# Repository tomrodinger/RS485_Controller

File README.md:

# Gearotons RS485 Controller

A programmable ESP32-S3 board with a half-duplex RS485 interface for Gearotons servomotors and other RS485 devices. The product includes an external antenna. One unit weighs **11.7 g including the antenna**.

## Documentation

[RS485 Controller hardware 0.5 documentation](https://9o.at/products/rs2/0.5) includes the datasheet, schematic and product photographs. The QR code printed on the PCB resolves to this page. Its content is generated from [`PRODUCT_DATA.yaml`](PRODUCT_DATA.yaml), using the same system as the RS485 Adapter and M17 Servomotor.

## Datasheet

[Download the RS485 Controller datasheet v1.0 (PDF)](datasheet/rs485_controller_datasheet_v1.0.pdf). Covers PCB revision 0.5, connector pinouts, two-motor wiring, mechanical dimensions, breakout headers, Arduino setup and the controller schematic.

## Hardware

The latest numbered PCB revision is **0.5**, in [`PCB/0.5`](PCB/0.5). Open `0.5.kicad_pro` in KiCad; the design was last saved with KiCad 9. The board outline is 48.89 × 36.88 mm, with a nominal PCB thickness of 1.6 mm. These dimensions exclude connector and antenna protrusions.

- ESP32-S3-MINI-1U module with external antenna connector.
- SP3485EN RS485 transceiver; automatic transmit direction circuitry.
- RS485 UART: GPIO4 TX and GPIO5 RX. The supplied demos use 230400 baud, 8N1.
- J5, marked **USB-C PROG**, connects to the ESP32-S3 native USB interface and the 5 V input rail.
- J3, marked **USB-C PD POWER IN**, uses a CH221K to request 20 V with R27 = 200 kΩ. R31 is an optional, unpopulated resistor in the standard design.
- J1, marked **POWER OUT**, exposes the J3 power rail directly: pin 1 positive, pin 2 GND. Actual output voltage depends on the connected supply and PD negotiation. Check the voltage before connecting motors.
- J2 pins 1–8: **GND, A, B, GND, A, B, 3.3 V, 5 V**. The two A/B/GND groups share one bus. Use the PCB labels to identify orientation.

Connect A to A, B to B, and controller GND to the motors' common ground. Motor power must use the appropriate motor supply, never J2's 3.3 V or 5 V pins. The board is not galvanically isolated. A board-level motor-current rating has not been established.

## Programming

Program the ESP32-S3 through J5 using a suitable ESP32-S3 toolchain, such as the Arduino ESP32 core with the Gearotons Servomotor library. Configure RS485 UART RX on GPIO5 and TX on GPIO4. The controller's USB-to-RS485 bridging and wireless application behavior depend on the firmware you install.

## Product images

[`images/rs485-controller`](images/rs485-controller) contains real product photographs, metadata-free JPEGs, full-resolution WebP images and 800-pixel WebP variants. [`manifest.json`](images/rs485-controller/manifest.json) supplies filenames, dimensions, alt text and original source hashes. These paths can be served directly from the public repository; use a pinned commit URL for immutable ecommerce assets.

## Validation of the 0.5 upload

On 2026-10-26, KiCad 9.0.7 error-level DRC with schematic parity reported zero violations, zero unconnected items and zero schematic parity issues. This is a design-file check, not an electrical or thermal qualification of manufactured hardware.

## Maintaining the documentation

The [maintainer handoff](datasheet/README.md#maintainer-handoff--4-november-2026), including its **5 November 2026 context-reset checkpoint**, records the accepted datasheet and diagram decisions, current 14-page PDF checksum, photo-edit sources, corrected pin/power guidance, build/verification commands, publication evidence and remaining limitations. Read it before continuing work after a context reset.

[`diagram-review/README.md`](diagram-review/README.md) preserves the artwork iterations and electrical-review history. [`motor_control_demo/README.md`](motor_control_demo/README.md) explains the separate Arduino examples. The unfinished archive in `PCB/V1_not_completed` is separate from the released PCB 0.5 design.

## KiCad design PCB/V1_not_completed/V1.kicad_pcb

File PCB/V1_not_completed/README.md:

# Unfinished design archive

This directory contains hardware work that predates the datasheet task and is retained as an unfinished development archive. Its library files and manufacturing exports are not the released RS485 Controller design.

The released product remains **RS2 / PCB revision 0.5** in [`../0.5`](../0.5), covered by datasheet document revision 1.0. Do not interpret this directory name as a released hardware version or use these fabrication exports as the production package for PCB 0.5.

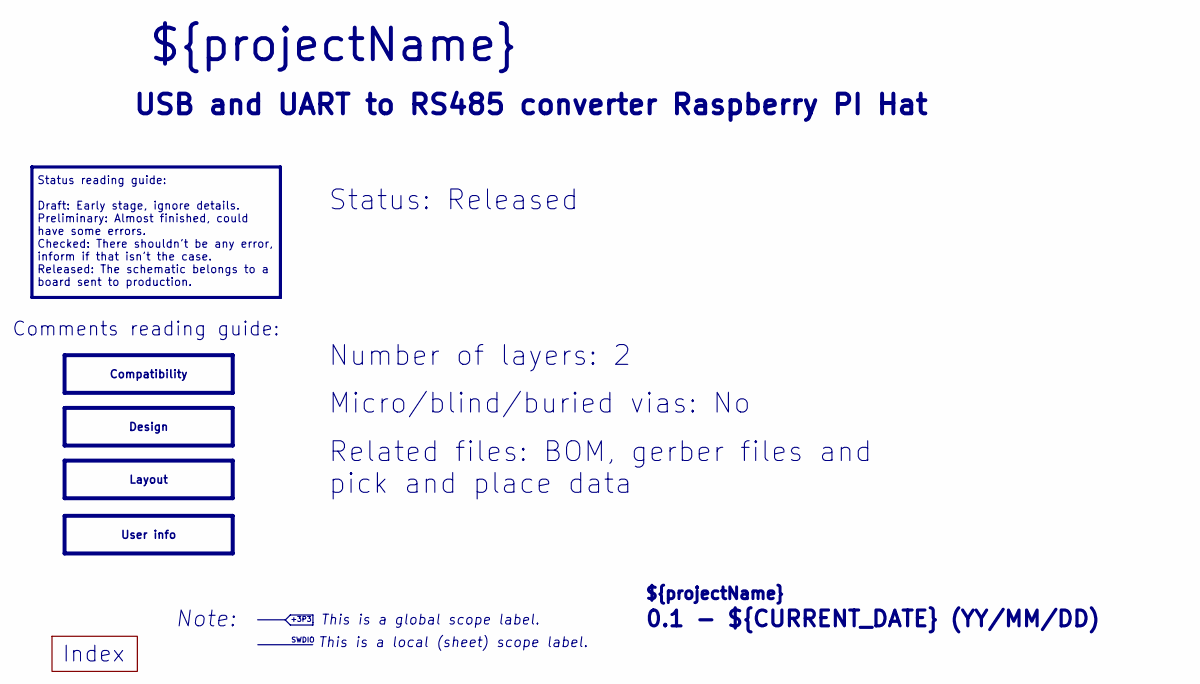
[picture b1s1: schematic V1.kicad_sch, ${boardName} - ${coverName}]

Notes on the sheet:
${REVISION} - ${CURRENT_DATE} (YY/MM/DD)
Status reading guide: Draft: Early stage, ignore details. Preliminary: Almost finished, could have some errors. Checked: There shouldn't be any error, inform if that isn't the case. Released: The schematic belongs to a board sent to production.
${projectName}
This is a global scope label.
Micro/blind/buried vias: No
Status: Released
Comments reading guide:
Note:
USB and UART to RS485 converter Raspberry PI Hat
Related files: BOM, gerber files and pick and place data
This is a local (sheet) scope label.
SWDIO
Index
+3P3
Number of layers: 2
Design
Compatibility
User info
Layout

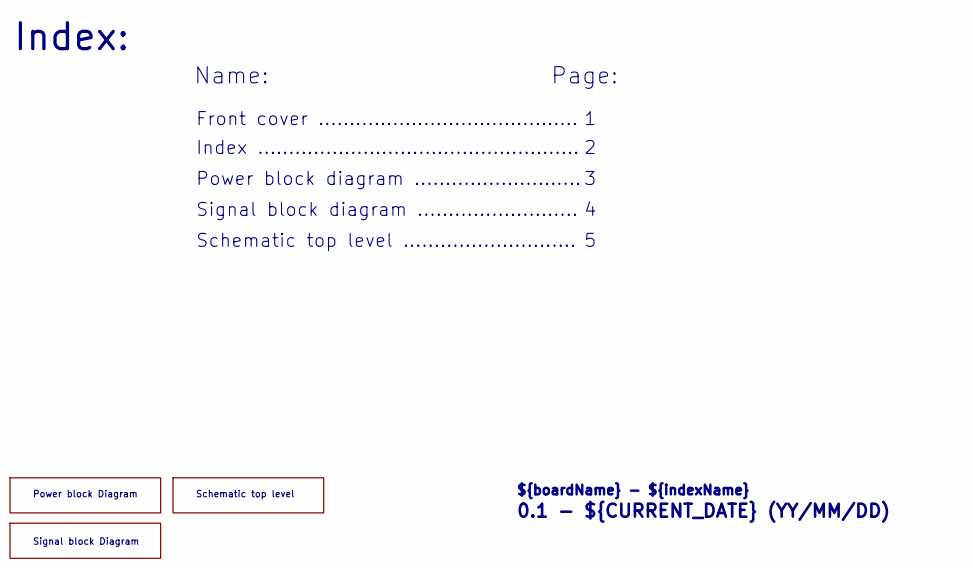
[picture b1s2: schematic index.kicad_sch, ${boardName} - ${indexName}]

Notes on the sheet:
Power block Diagram
Front cover ..........................................
Schematic top level
${boardName} - ${indexName}
Schematic top level ............................
Index ....................................................
${REVISION} - ${CURRENT_DATE} (YY/MM/DD)
Signal block diagram ..........................
Signal block Diagram
Name:
Page:
Power block diagram ...........................
Index:

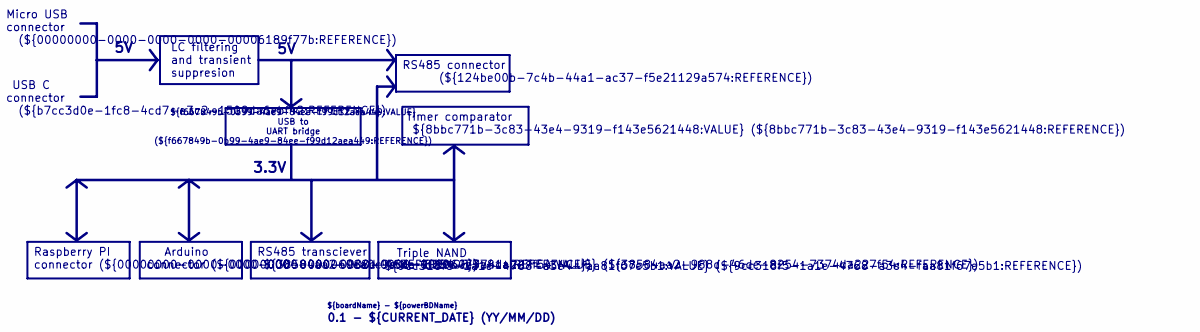
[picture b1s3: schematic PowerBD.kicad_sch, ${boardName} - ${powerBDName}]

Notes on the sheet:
Arduino connector (${00000000-0000-0000-0000-000060e9a81a:REFERENCE})
RS485 connector (${124be00b-7c4b-44a1-ac37-f5e21129a574:REFERENCE})
Triple NAND ${9cc318f5-1a1e-4768-a3e4-faa81f67e5b1:VALUE} (${9cc318f5-1a1e-4768-a3e4-faa81f67e5b1:REFERENCE})
Raspberry PI connector (${00000000-0000-0000-0000-000060ea0c9e:REFERENCE})
RS485 transciever ${38584aa2-988d-46de-8254-7374da227f54:VALUE} (${38584aa2-988d-46de-8254-7374da227f54:REFERENCE})
LC filtering and transient suppresion
${REVISION} - ${CURRENT_DATE} (YY/MM/DD)
USB C connector (${b7cc3d0e-1fc8-4cd7-a3c2-1509da6ebf42:REFERENCE})
Timer comparator ${8bbc771b-3c83-43e4-9319-f143e5621448:VALUE} (${8bbc771b-3c83-43e4-9319-f143e5621448:REFERENCE})
${boardName} - ${powerBDName}
Micro USB connector (${00000000-0000-0000-0000-00006189f77b:REFERENCE})
3.3V
${f667849b-0b99-4ae9-84ee-f99d12aea449:VALUE} USB to UART bridge (${f667849b-0b99-4ae9-84ee-f99d12aea449:REFERENCE})

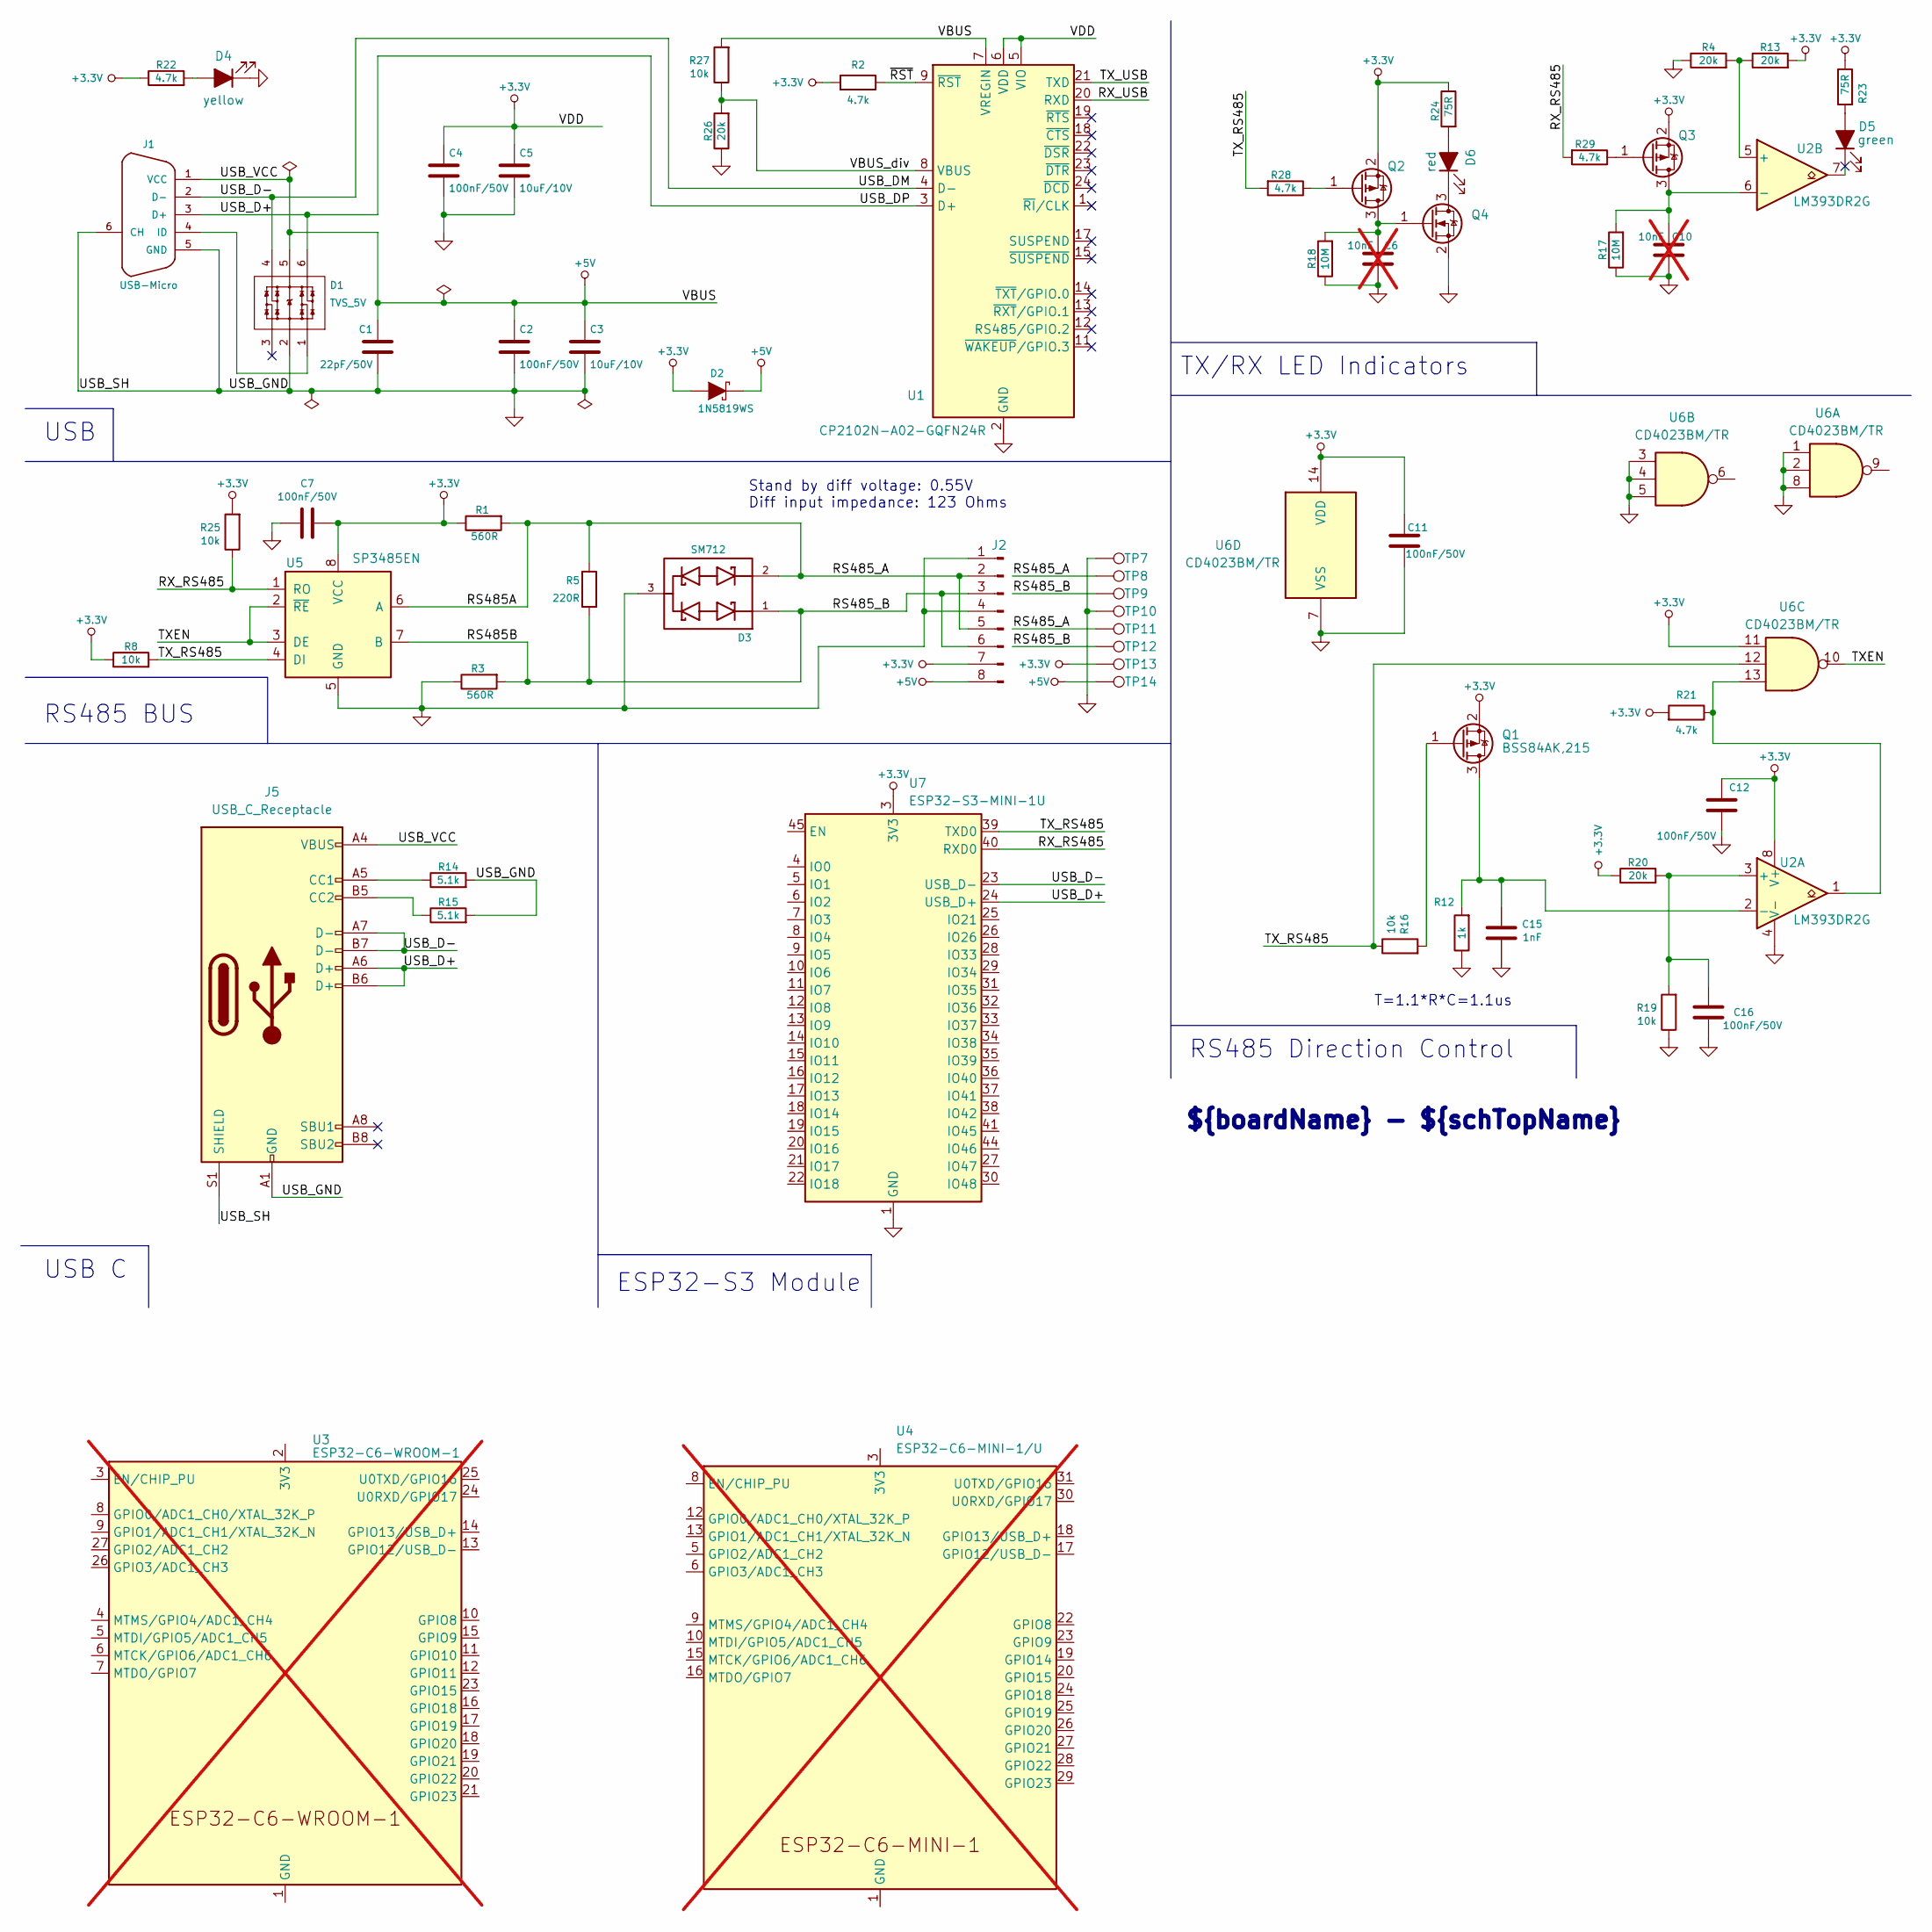
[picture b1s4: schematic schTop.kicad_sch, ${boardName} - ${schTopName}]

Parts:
C1: 22pF/50V; C_0603_1608Metric; Tolerance 5%; PartNumber CL10C220JB8NNNC; Digikey 1276-1023-1-ND
C2, C4, C7, C11, C12, C16: 100nF/50V; C_0603_1608Metric; Tolerance 10%; PartNumber CC0603KRX7R9BB104; Digikey 1276-6854-1-ND
C3, C5: 10uF/10V; C_0603_1608Metric; Tolerance 10%; PartNumber CL10A106KP8NNNC; LCSC C19702
C6: 10nF; C_0603_1608Metric; Tolerance 10%; PartNumber 0603B103K500NT; LCSC C57112; not fitted
C10: 10nF; C_0603_1608Metric; Tolerance 10%; PartNumber 0603B103K500NT; Digikey ---; not fitted
C15: 1nF; C_0603_1608Metric; Tolerance 10%; PartNumber CL10B102KB8NNNC; LCSC C1588
D1: TVS_5V; SOT23-6L; Tolerance _; PartNumber TPIP4220CZ6; Digikey !1727-2751-1-ND
D2: 1N5819WS; SOD323; LCSC C191023
D3: SM712; SOT23-3; Tolerance _; PartNumber SM712; Digikey !F6450CT-ND
D4: yellow; LED_0805_2012Metric; PartNumber KT-0805Y; LCSC C2296
D5: green; LED_0805_2012Metric; PartNumber KT-0805G; LCSC C2297
D6: red; LED_0805_2012Metric; PartNumber NCD0805R1; LCSC C84256
J1: USB-Micro; usb-MicroXNJ; Tolerance _; PartNumber MicroXNJ; Digikey !732-5961-1-ND
J2: TSM-108-01-T-SH-A-P-TR; SAMTEC_TSM-108-01-T-SH-A-P-TR_hole1.5mm
J5: USB_C_Receptacle; USB_C_Receptacle_Palconn_UTC16-G; LCSC C2765186
Q1, Q2, Q3: BSS84AK,215; SOT-23; Tolerance _; PartNumber BSS84AK,215; Digikey ---
Q4: Q_NMOS_GSD; SOT-23; Part Number 2N7002; LCSC C8545
R1, R3: 560R; R_0603_1608Metric; Tolerance 1%; PartNumber 0603WAF5600T5E; LCSC C23204
R2, R21, R22, R28, R29: 4.7k; R_0603_1608Metric; Tolerance 1%; PartNumber 0603WAF4701T5E; LCSC C23162
R4, R13, R20, R26: 20k; R_0603_1608Metric; Tolerance 1%; PartNumber 0603WAF2002T5E; LCSC C4184
R5: 220R; R_0603_1608Metric; Tolerance 5%; PartNumber 0603WAF2200T5E; LCSC C22962
R8, R16, R19, R25, R27: 10k; R_0603_1608Metric; Tolerance 1%; PartNumber 0603WAF1002T5E; LCSC C25804
R12: 1k; R_0603_1608Metric; Tolerance 1%; PartNumber 0603WAF1001T5E; Digikey 311-1.00KHRCT-ND
R14, R15: 5.1k; R_0402_1005Metric; Tolerance 1%; LCSC C25905
R17, R18: 10M; R_0603_1608Metric; PartNumber 0603WAF1005T5E; LCSC C7250
R23, R24: 75R; R_0603_1608Metric; Tolerance 1%; PartNumber 0603WAF750JT5E; LCSC C4275
TP7, TP8, TP9, TP10, TP11, TP12, TP13, TP14: TestPoint; testpoint_no_border
U1: CP2102N-A02-GQFN24R; QFN-24-1EP_4x4mm_P0.5mm_EP2.6x2.6mm; Tolerance _; PartNumber CP2102N-A02-GQFN24R; Digikey _
U2: LM393DR2G; SOIC-8_3.9x4.9mm_P1.27mm; Tolerance _; PartNumber LM393DR2G; Digikey _
U3: ESP32-C6-WROOM-1; not fitted
U4: ESP32-C6-MINI-1/U; ESP32-C6-MINI-1; not fitted
U5: SP3485EN; SOIC-8_3.9x4.9mm_P1.27mm; Tolerance _; PartNumber SP3485EN-L/TR; LCSC C8963
U6: CD4023BM/TR; SOIC-14_3.9x8.7mm_P1.27mm; Tolerance _; PartNumber CD4023BM/TR; Digikey _
U7: ESP32-S3-MINI-1U; ESP32-S2-MINI-1U

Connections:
+3.3V: C4.1, C5.1, C7.2, C11.2, C12.2, D2.1 (A), J2.7, Q1.2 (S), Q2.2 (S), Q3.2 (S), R1.1, R2.2, R8.1, R13.2, R20.1, R21.2, R22.1, R23.1, R24.1, R25.2, TP13.1, U1.5 (VIO), U1.6 (VDD), U2.8 (V+), U5.8 (VCC), U6.11, U6.14 (VDD), U7.3 (3V3); also elsewhere on the board
+5V: C1.1, C2.1, C3.1, D1.5 (VDD), D2.2 (K), J1.1 (VCC), J2.8, J5.A4 (VBUS), J5.A9 (VBUS), J5.B4 (VBUS), J5.B9 (VBUS), R27.2, TP14.1, U1.7 (VREGIN)
/index/schTop/RS485A: D3.2 (cathode), J2.2, J2.5, R1.2, R5.1, TP8.1, TP11.1, U5.6 (A)
/index/schTop/RS485B: D3.1 (Anode), J2.3, J2.6, R3.2, R5.2, TP9.1, TP12.1, U5.7 (B)
/index/schTop/RX_RS485: R25.1, R29.2, U5.1 (RO), U7.40 (RXD0)
/index/schTop/RX_USB: U1.20 (RXD)
/index/schTop/TXEN: U5.2 (~RE), U5.3 (DE), U6.10
/index/schTop/TX_RS485: R8.2, R16.1, R28.2, U5.4 (DI), U6.12, U7.39 (TXD0)
/index/schTop/TX_USB: U1.21 (TXD)
/index/schTop/USB_D+: D1.6 (IO4), J1.3 (D+), J5.A6 (D+), J5.B6 (D+), U1.3 (D+), U7.24 (USB_D+)
/index/schTop/USB_D-: D1.4 (IO3), J1.2 (D-), J5.A7 (D-), J5.B7 (D-), U1.4 (D-), U7.23 (USB_D-)
/index/schTop/VBUS_div: R26.2, R27.1, U1.8 (VBUS)
/index/schTop/~RST: R2.1, U1.9 (~RST)
GND: C1.2, C2.2, C3.2, C4.2, C5.2, C6.1, C7.1, C10.1, C11.1, C12.1, C15.1, C16.1, D1.2 (GND), D3.3 (AK), D4.1 (K), J1.5 (GND), J1.6 (CH), J2.1, J2.4, J5.A1 (GND), J5.A12 (GND), J5.B1 (GND), J5.B12 (GND), J5.S1 (SHIELD), Q4.2 (S), R3.1, R4.1, R12.1, R14.2, R15.2, R17.1, R18.1, R19.1, R26.1, TP7.1, TP10.1, U1.2 (GND), U1.25 (GND), U2.4 (V-), U5.5 (GND), U6.1, U6.2, U6.3, U6.4, U6.5, U6.7 (VSS), U6.8, U7.1 (GND), U7.2 (GND), U7.42 (GND), U7.43 (GND), U7.46 (GND), U7.47 (GND), U7.48 (GND), U7.49 (GND), U7.50 (GND), U7.51 (GND), U7.52 (GND), U7.53 (GND), U7.54 (GND), U7.55 (GND), U7.56 (GND), U7.57 (GND), U7.58 (GND), U7.59 (GND), U7.60 (GND), U7.61 (GND), U7.62 (GND), U7.63 (GND), U7.64 (GND), U7.65 (GND); also elsewhere on the board
unnamed: D1.1 (IO1), J1.4 (ID)
unnamed: D4.2 (A), R22.2
unnamed: D5.2 (A), R23.2
unnamed: D6.2 (A), R24.2
unnamed: D6.1 (K), Q4.3 (D)
unnamed: J5.A5 (CC1), R14.1
unnamed: J5.B5 (CC2), R15.1
unnamed: C15.2, Q1.3 (D), R12.2, U2.2 (-)
unnamed: Q1.1 (G), R16.2
unnamed: C6.2, Q2.3 (D), Q4.1 (G), R18.2
unnamed: Q2.1 (G), R28.1
unnamed: C10.2, Q3.3 (D), R17.2, U2.6 (-)
unnamed: Q3.1 (G), R29.1
unnamed: R21.1, U2.1, U6.13
unnamed: C16.2, R19.2, R20.2, U2.3 (+)
unnamed: R4.2, R13.1, U2.5 (+)
unnamed: U3.1 (GND), U3.28 (GND), U3.29 (GND)
unnamed: U4.1 (GND), U4.2 (GND), U4.11 (GND), U4.14 (GND), U4.36 (GND), U4.37 (GND), U4.38 (GND), U4.39 (GND), U4.40 (GND), U4.41 (GND), U4.42 (GND), U4.43 (GND), U4.44 (GND), U4.45 (GND), U4.46 (GND), U4.47 (GND), U4.48 (GND), U4.49 (GND), U4.50 (GND), U4.51 (GND), U4.52 (GND), U4.53 (GND)

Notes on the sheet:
Stand by diff voltage: 0.55V Diff input impedance: 123 Ohms
RS485 BUS
T=1.1*R*C=1.1us
TX/RX LED Indicators
USB C
USB
RS485 Direction Control
${boardName} - ${schTopName}
ESP32-S3 Module

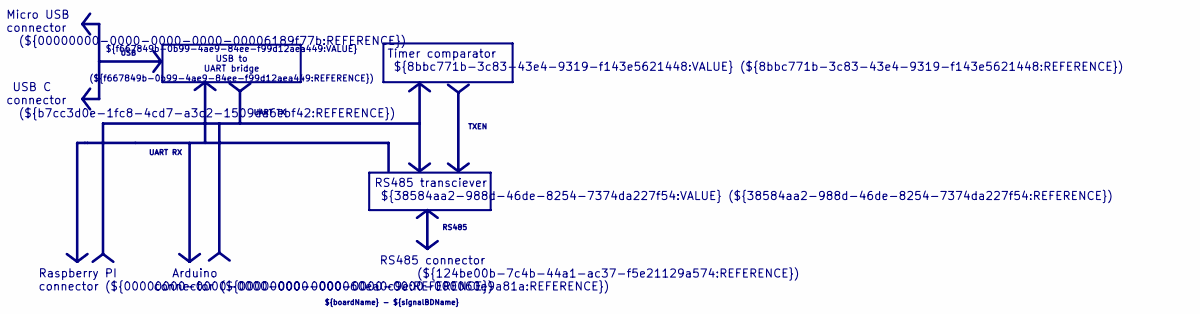
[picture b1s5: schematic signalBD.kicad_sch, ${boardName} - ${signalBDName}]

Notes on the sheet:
RS485 transciever ${38584aa2-988d-46de-8254-7374da227f54:VALUE} (${38584aa2-988d-46de-8254-7374da227f54:REFERENCE})
${boardName} - ${signalBDName}
RS485 connector (${124be00b-7c4b-44a1-ac37-f5e21129a574:REFERENCE})
Raspberry PI connector (${00000000-0000-0000-0000-000060ea0c9e:REFERENCE})
UART TX
USB C connector (${b7cc3d0e-1fc8-4cd7-a3c2-1509da6ebf42:REFERENCE})
UART RX
RS485
TXEN
USB
Timer comparator ${8bbc771b-3c83-43e4-9319-f143e5621448:VALUE} (${8bbc771b-3c83-43e4-9319-f143e5621448:REFERENCE})
Arduino connector (${00000000-0000-0000-0000-000060e9a81a:REFERENCE})
Micro USB connector (${00000000-0000-0000-0000-00006189f77b:REFERENCE})
${f667849b-0b99-4ae9-84ee-f99d12aea449:VALUE} USB to UART bridge (${f667849b-0b99-4ae9-84ee-f99d12aea449:REFERENCE})

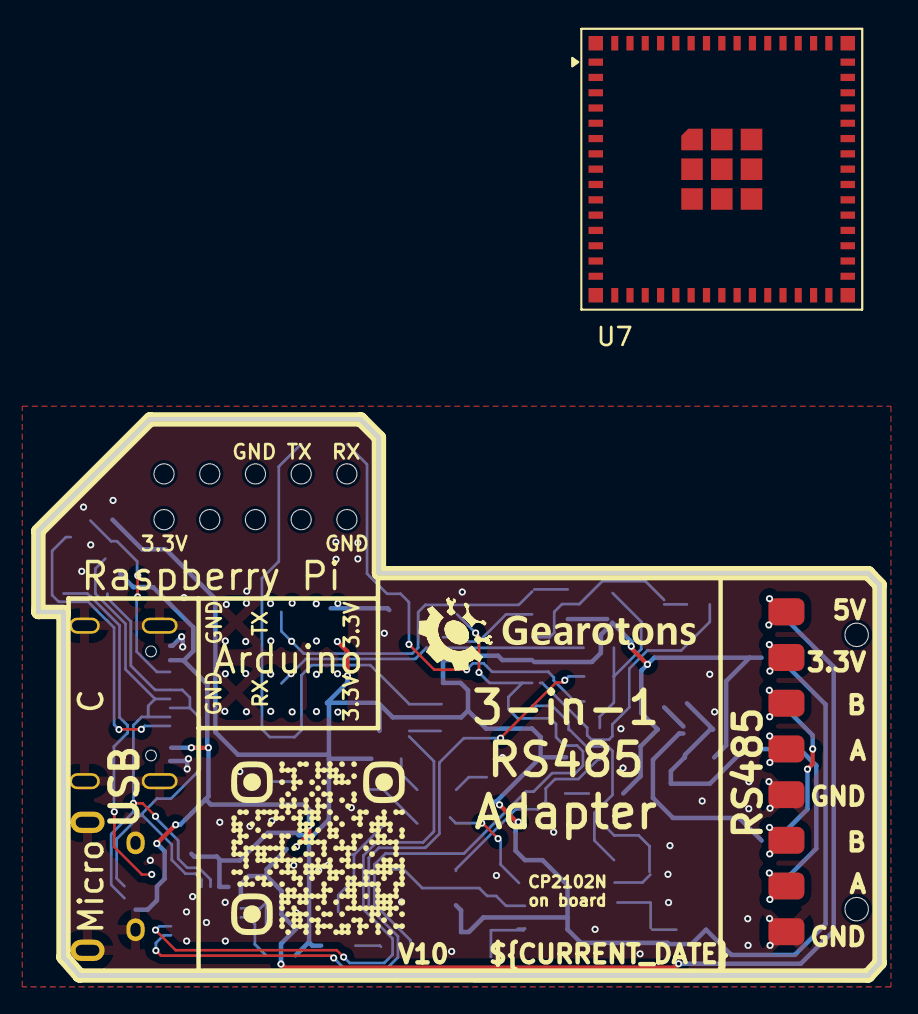
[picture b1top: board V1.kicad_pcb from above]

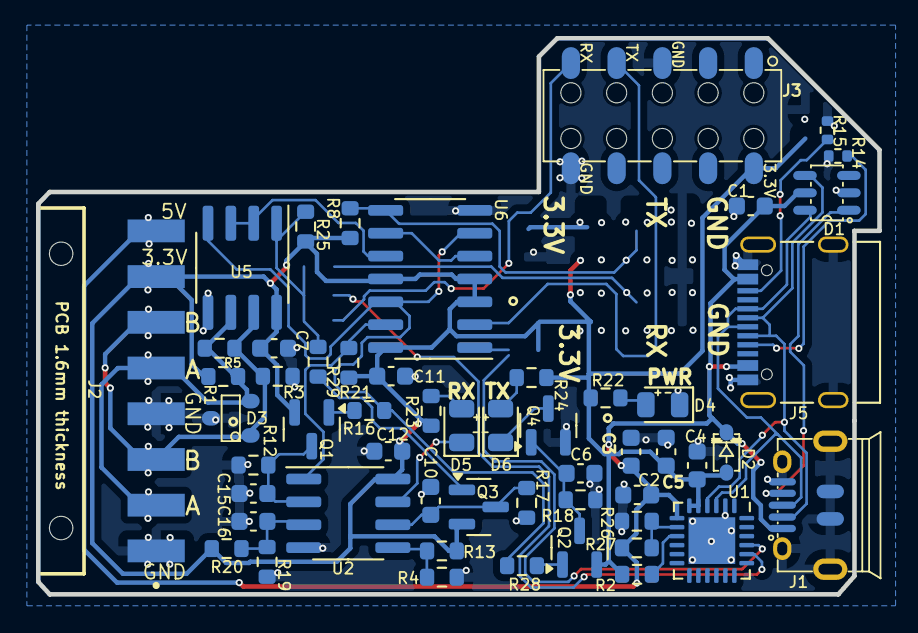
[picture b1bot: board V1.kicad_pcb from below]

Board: 2 copper layers, 46.7 x 30.9 mm, 63 parts (54 on the bottom side), 28 nets.

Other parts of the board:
J3: Raspberry-Pi_2x5-Pin_Header; con-WR-PHD-61031021821

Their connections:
+3.3V: J3.2 (3.3V); also elsewhere on the board
GND: J3.5 (GND), J3.10 (GND); also elsewhere on the board

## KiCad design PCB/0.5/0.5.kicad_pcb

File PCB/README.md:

# PCB revision guide

- `0.5/`: latest numbered design. Schematic and PCB revision fields are 0.5, dated 2025-11-29. Production outputs and assembly CSVs are included as supplied.
- `0.2/`, `0.1/`: historical revisions.

Open the matching `.kicad_pro`, then its root schematic. Footprints and symbols used by a design are embedded in the PCB and schematic. Some historical library-table entries still refer to the original designer's local libraries; replacing a symbol may require configuring those libraries.

Do not use the ignored historical `0.5.xml` export as a source for the controller pinout: it describes an older, different adapter. Regenerate netlists from the current root schematic. The revision 0.5 schematic marks R31 (62 kΩ) as DNP; the standard PD request uses R27 (200 kΩ) alone.

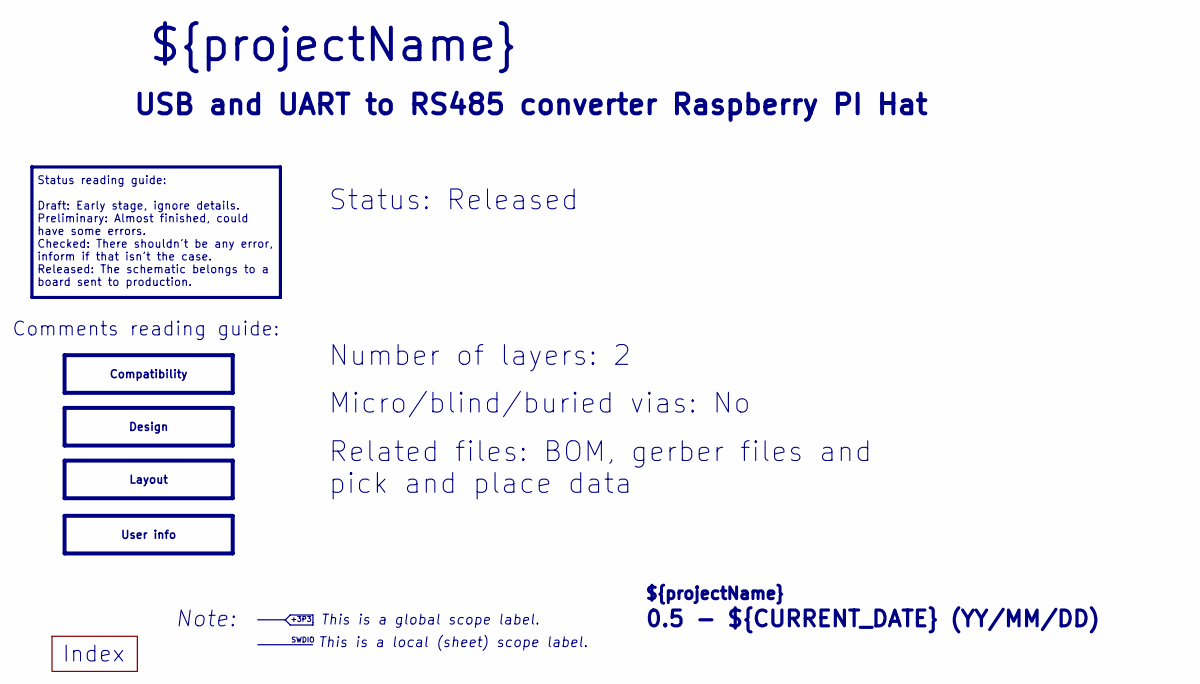
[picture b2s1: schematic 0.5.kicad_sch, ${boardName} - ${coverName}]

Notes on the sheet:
${REVISION} - ${CURRENT_DATE} (YY/MM/DD)
Status reading guide: Draft: Early stage, ignore details. Preliminary: Almost finished, could have some errors. Checked: There shouldn't be any error, inform if that isn't the case. Released: The schematic belongs to a board sent to production.
${projectName}
This is a global scope label.
Micro/blind/buried vias: No
Status: Released
Comments reading guide:
Note:
USB and UART to RS485 converter Raspberry PI Hat
Related files: BOM, gerber files and pick and place data
This is a local (sheet) scope label.
SWDIO
Index
+3P3
Number of layers: 2
Design
Compatibility
User info
Layout

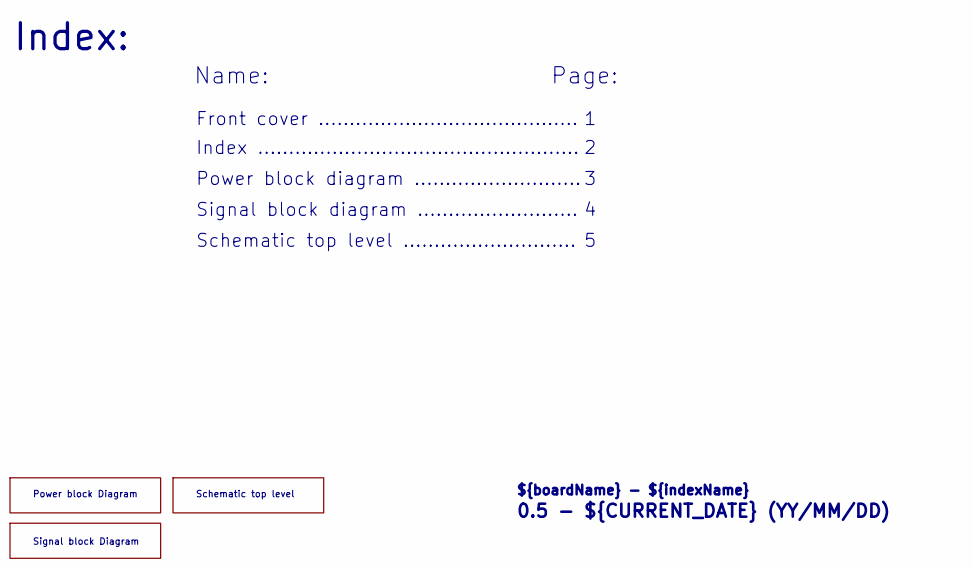
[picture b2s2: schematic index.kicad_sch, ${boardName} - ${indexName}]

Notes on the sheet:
Power block Diagram
Front cover ..........................................
Schematic top level
${boardName} - ${indexName}
Schematic top level ............................
Index ....................................................
${REVISION} - ${CURRENT_DATE} (YY/MM/DD)
Signal block diagram ..........................
Signal block Diagram
Name:
Page:
Power block diagram ...........................
Index:

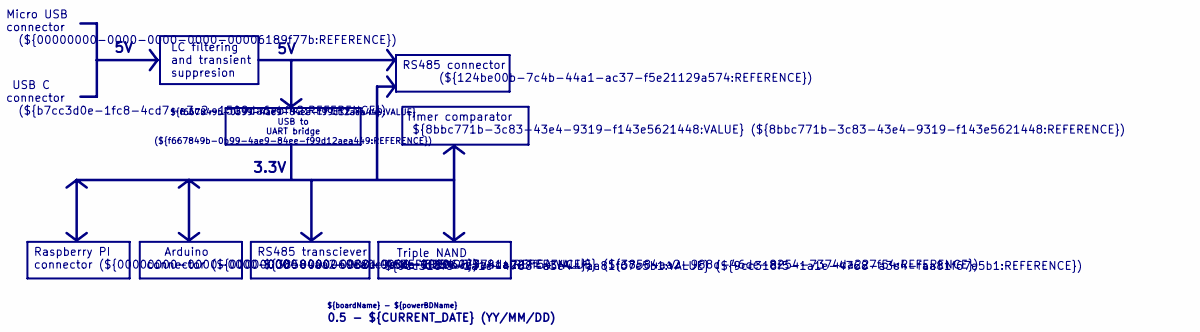
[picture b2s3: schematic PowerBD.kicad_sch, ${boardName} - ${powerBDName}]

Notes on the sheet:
Arduino connector (${00000000-0000-0000-0000-000060e9a81a:REFERENCE})
RS485 connector (${124be00b-7c4b-44a1-ac37-f5e21129a574:REFERENCE})
Triple NAND ${9cc318f5-1a1e-4768-a3e4-faa81f67e5b1:VALUE} (${9cc318f5-1a1e-4768-a3e4-faa81f67e5b1:REFERENCE})
Raspberry PI connector (${00000000-0000-0000-0000-000060ea0c9e:REFERENCE})
RS485 transciever ${38584aa2-988d-46de-8254-7374da227f54:VALUE} (${38584aa2-988d-46de-8254-7374da227f54:REFERENCE})
LC filtering and transient suppresion
${REVISION} - ${CURRENT_DATE} (YY/MM/DD)
USB C connector (${b7cc3d0e-1fc8-4cd7-a3c2-1509da6ebf42:REFERENCE})
Timer comparator ${8bbc771b-3c83-43e4-9319-f143e5621448:VALUE} (${8bbc771b-3c83-43e4-9319-f143e5621448:REFERENCE})
${boardName} - ${powerBDName}
Micro USB connector (${00000000-0000-0000-0000-00006189f77b:REFERENCE})
3.3V
${f667849b-0b99-4ae9-84ee-f99d12aea449:VALUE} USB to UART bridge (${f667849b-0b99-4ae9-84ee-f99d12aea449:REFERENCE})
